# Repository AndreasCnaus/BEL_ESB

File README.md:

# Hardware Setup
- RF Breakout Board (see also Hardware Section)
- Bosch BME280 Sensor
- RF-Antenna

# Verification with nRF-Connect

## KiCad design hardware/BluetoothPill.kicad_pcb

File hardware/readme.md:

# RF Breakout Board

USB Powered STM32WB55 based breakout board for wireless applications within 2.4GHz ISM-Band (e.g BLE). 

# Characteristics
Input Voltage-Range: &nbsp; 3.4V - 5.5V <br>
Output Voltage: &nbsp; 3.3V <br>
Crystals: &nbsp; HSE: 32MHz, LSE: 32.768kHz <br> 
MCU: &nbsp; STM32WB55CEU6 <br>
SMPS-Support: &nbsp;  for low power mode <br>
BOOT0/User-Button: &nbsp; boots from USB when pushed during power up <br>
LED's:  &nbsp; Power-Led (orange), User-Led (blue) <br>
Serial Wire Debug with Tag-Connec <br>

## Connectivity
USB-FS with 12Mb/s <br>
I2C1: &nbsp; (SDA, SCL) <br>
UART1: &nbsp; (Tx, Rx) <br>
SPI1: &nbsp; (NSS, SCK, MISO, MOSI) <br>
RF: &nbsp; 2.4GHz ISM-Band, BLE 5.4, IEEE 802.15.4 (Zigbee 3.0, Thread 1.3) <br>

# Links
This board was designed according to the following tutorial with a few changes: &nbsp; https://youtu.be/nkHFoxe0mrU?si=10UZT0h6SDpFT777 <br>
STM32WB55-Datasheet: &nbsp; https://www.st.com/resource/en/datasheet/stm32wb55cc.pdf <br>

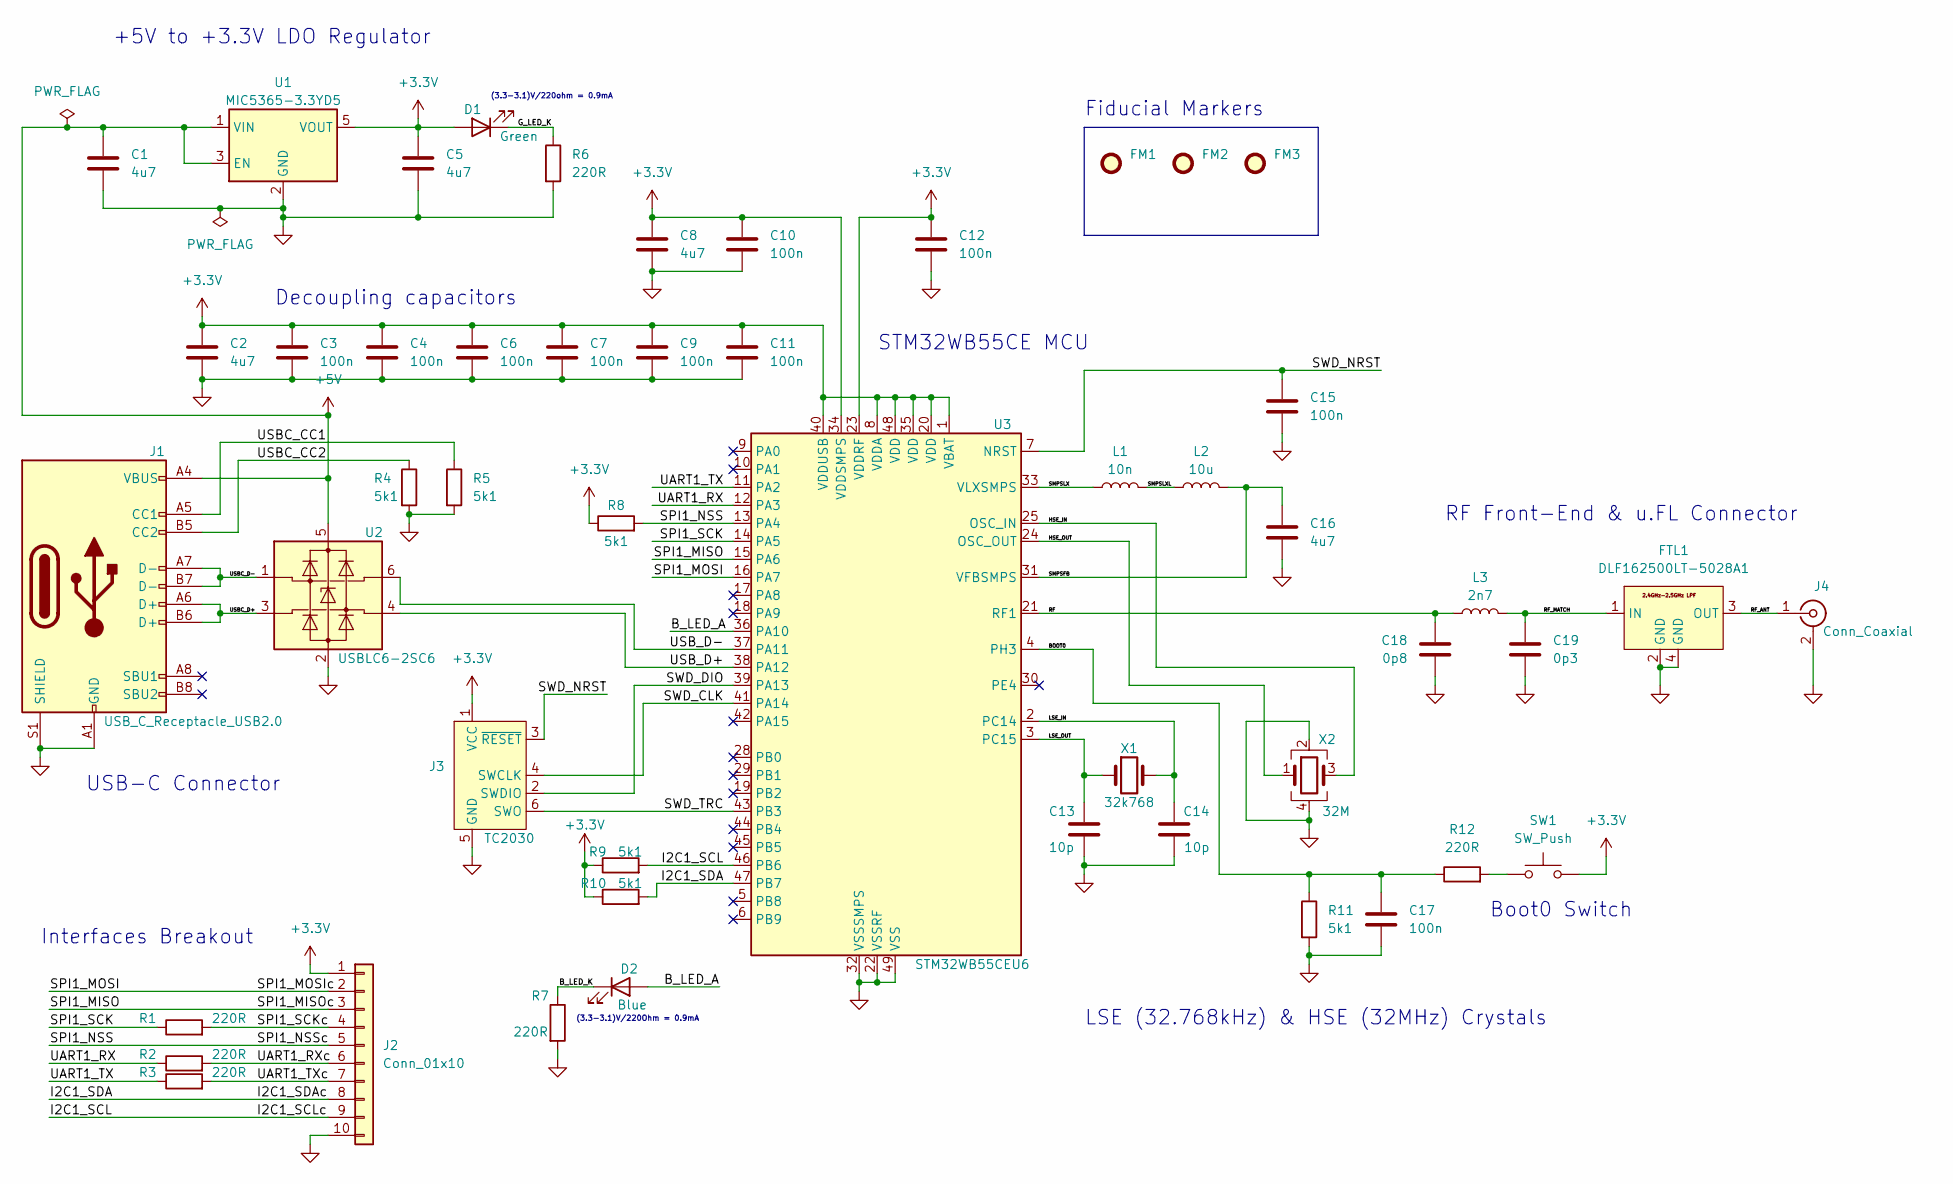
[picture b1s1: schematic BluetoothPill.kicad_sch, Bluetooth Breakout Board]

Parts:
C1, C2, C5, C8, C16: 4u7; C_0603_1608Metric; Manufacturer Part Numb KGM15CR51E475KT
C3, C4, C6, C7, C9, C10, C11, C12, C15, C17: 100n; C_0402_1005Metric; Manufacturer Part Numb 885012205086
C13, C14: 10p; C_0402_1005Metric; Manufacturer Part Numb C0402C100K8HACAUTO
C18: 0p8; C_0402_1005Metric; Manufacturer Part Numb GRM1555C1HR80BA01D
C19: 0p3; C_0402_1005Metric; Manufacturer Part Numb GRM1555C1HR30WA01D
D1: Green; LED_0402_1005Metric; Manufacturer Part Numb LTST-C281KGKT
D2: Blue; LED_0402_1005Metric; Manufacturer Part Numb VLMB1500-GS08
FM1, FM2, FM3: Fiducial; Fiducial_1mm_Mask2mm
FTL1: DLF162500LT-5028A1; Manufacturer Part Numb DLF162500LT-5028A1
J1: USB_C_Receptacle_USB2.0; USB_C_Receptacle_GCT_USB4105-xx-A_16P_TopMnt_Horizontal; Manufacturer Part Numb USB4105-GF-A
J2: Conn_01x10; PinHeader_1x10_P2.54mm_Vertical
J3: TC2030; Tag-Connect_TC2030-IDC-FP_2x03_P1.27mm_Vertical
J4: Conn_Coaxial; U.FL_Hirose_U.FL-R-SMT-1_Vertical; Manufacturer Part Numb U.FL-R-SMT(01)
L1: 10n; L_0402_1005Metric; Manufacturer Part Numb LQG15WZ10NJ02D
L2: 10u; L_0805_2012Metric; Manufacturer Part Numb LQM21FN100M70L
L3: 2n7; L_0402_1005Metric; Manufacturer Part Numb LQG15HS2N7S02D
R1, R2, R3, R6, R7, R12: 220R; R_0402_1005Metric; Manufacturer Part Numb AF0402JR-07220RL
R4, R5, R8, R9, R10, R11: 5k1; R_0402_1005Metric; Manufacturer Part Numb ERJ-2RKF5101X
SW1: SW_Push; SW_SPST_CK_RS282G05A3; Manufacturer Part Numb RS282G05A3SMRT
U1: MIC5365-3.3YD5; SOT-23-5; Manufacturer Part Numb MIC5365-3.3YD5-TR
U2: USBLC6-2SC6; SOT-23-6; Manufacturer Part Numb USBLC6-2SC6
U3: STM32WB55CEU6; QFN-48-1EP_7x7mm_P0.5mm_EP5.6x5.6mm; Manufacturer Part Numb STM32WB55CEU6
X1: 32k768; Crystal_SMD_2012-2Pin_2.0x1.2mm; Manufacturer Part Numb NX2012SA-32.768K-STD-MUB-1
X2: 32M; Crystal_SMD_2016-4Pin_2.0x1.6mm; Manufacturer Part Numb NX2016SA-32M-EXS00A-CS06465

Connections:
+3.3V: C2.1, C3.1, C4.1, C5.1, C6.1, C7.1, C8.1, C9.1, C10.1, C11.1, C12.1, D1.2 (A), J2.1, J3.1 (VCC), R8.1, R9.1, R10.1, SW1.2, U1.5 (VOUT), U3.1 (VBAT), U3.8 (VDDA), U3.20 (VDD), U3.23 (VDDRF), U3.34 (VDDSMPS), U3.35 (VDD), U3.40 (VDDUSB), U3.48 (VDD)
+5V: C1.1, J1.A4 (VBUS), J1.A9 (VBUS), J1.B4 (VBUS), J1.B9 (VBUS), U1.1 (VIN), U1.3 (EN), U2.5 (VBUS)
/BOOT0: C17.1, R11.1, R12.1, U3.4 (PH3)
/B_LED_A: D2.2 (A), U3.36 (PA10)
/B_LED_K: D2.1 (K), R7.1
/G_LED_K: D1.1 (K), R6.1
/HSE_IN: U3.25 (OSC_IN), X2.3
/HSE_OUT: U3.24 (OSC_OUT), X2.1
/I2C1_SCL: J2.9, R9.2, U3.46 (PB6)
/I2C1_SDA: J2.8, R10.2, U3.47 (PB7)
/LSE_IN: C14.1, U3.2 (PC14), X1.2
/LSE_OUT: C13.1, U3.3 (PC15), X1.1
/RF: C18.1, L3.1, U3.21 (RF1)
/RF_ANT: FTL1.3 (OUT), J4.1 (In)
/RF_MATCH: C19.1, FTL1.1 (IN), L3.2
/SMPSFB: C16.1, L2.2, U3.31 (VFBSMPS)
/SMPSLX: L1.1, U3.33 (VLXSMPS)
/SMPSLXL: L1.2, L2.1
/SPI1_MISO: J2.3, U3.15 (PA6)
/SPI1_MOSI: J2.2, U3.16 (PA7)
/SPI1_NSS: J2.5, R8.2, U3.13 (PA4)
/SPI1_SCK: R1.1, U3.14 (PA5)
/SPI1_SCKc: J2.4, R1.2
/SWD_CLK: J3.4 (SWCLK), U3.41 (PA14)
/SWD_DIO: J3.2 (SWDIO), U3.39 (PA13)
/SWD_NRST: C15.1, J3.3 (~RESET), U3.7 (NRST)
/SWD_TRC: J3.6 (SWO), U3.43 (PB3)
/UART1_RX: R2.1, U3.12 (PA3)
/UART1_RXc: J2.6, R2.2
/UART1_TX: R3.1, U3.11 (PA2)
/UART1_TXc: J2.7, R3.2
/USBC_CC1: J1.A5 (CC1), R5.1
/USBC_CC2: J1.B5 (CC2), R4.1
/USBC_D+: J1.A6 (D+), J1.B6 (D+), U2.3 (I/O1)
/USBC_D-: J1.A7 (D-), J1.B7 (D-), U2.1 (I/O1)
/USB_D+: U2.4 (I/O2), U3.38 (PA12)
/USB_D-: U2.6 (I/O2), U3.37 (PA11)
GND: C1.2, C2.2, C3.2, C4.2, C5.2, C6.2, C7.2, C8.2, C9.2, C10.2, C11.2, C12.2, C13.2, C14.2, C15.2, C16.2, C17.2, C18.2, C19.2, FTL1.2 (GND), FTL1.4 (GND), J1.A1 (GND), J1.A12 (GND), J1.B1 (GND), J1.B12 (GND), J1.S1 (SHIELD), J2.10, J3.5 (GND), J4.2 (Ext), R4.2, R5.2, R6.2, R7.2, R11.2, U1.2 (GND), U2.2 (GND), U3.22 (VSSRF), U3.32 (VSSSMPS), U3.49 (VSS), X2.2, X2.4
unnamed: R12.2, SW1.1

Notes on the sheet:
Fiducial Markers
USB-C Connector
RF Front-End & u.FL Connector
+5V to +3.3V LDO Regulator
(3.3-3.1)V/220Ohm = 0.9mA
LSE (32.768kHz) & HSE (32MHz) Crystals
Interfaces Breakout
Decoupling capacitors
Boot0 Switch
(3.3-3.1)V/220ohm = 0.9mA
STM32WB55CE MCU

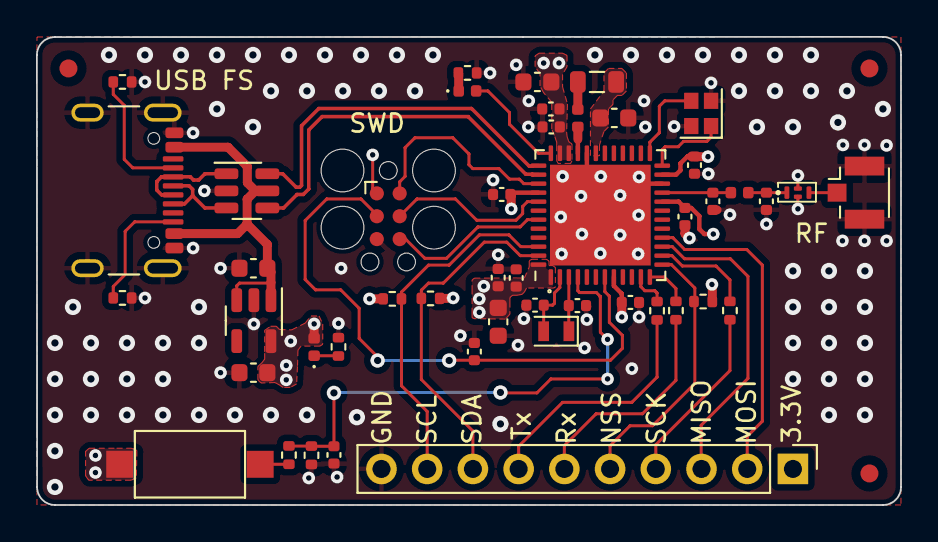
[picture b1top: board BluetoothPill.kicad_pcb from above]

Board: 4 copper layers, 48.0 x 26.0 mm, 50 parts (0 on the bottom side), 39 nets.

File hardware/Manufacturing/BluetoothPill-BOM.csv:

Designator,Quantity,Value,Footprint,Description,Manufacturer,Manufacturer Part Number,Distributor Link
"C1, C2, C5, C8, C16",5,4u7,Capacitor_SMD:C_0603_1608Metric,Unpolarized capacitor,KYOCERA AVX,KGM15CR51E475KT,https://www.mouser.de/ProductDetail/KYOCERA-AVX/KGM15CR51E47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
"C3, C4, C6, C7, C9, C10, C11, C12, C15, C17",10,100n,Capacitor_SMD:C_0402_1005Metric,Unpolarized capacitor,Wurth Elektronik,885012205086,https://www.mouser.de/ProductDetail/Wurth-Elektronik/8850122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
"C13, C14",2,10p,Capacitor_SMD:C_0402_1005Metric,Unpolarized capacitor,KEMET,C0402C100K8HACAUTO,https://www.mouser.de/ProductDetail/KEMET/C0402C100K8HACAUTO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
C18,1,0p8,Capacitor_SMD:C_0402_1005Metric,Unpolarized capacitor,Murata Electronics,GRM1555C1HR80BA01D,https://www.mouser.de/ProductDetail/Murata-Electronics/GRM15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
C19,1,0p3,Capacitor_SMD:C_0402_1005Metric,Unpolarized capacitor,Murata Electronics,GRM1555C1HR30WA01D,https://www.mouser.de/ProductDetail/Murata-Electronics/GRM15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
D1,1,Green,LED_SMD:LED_0402_1005Metric,Light emitting diode,Lite-On,LTST-C281KGKT,https://www.mouser.de/ProductDetail/Lite-On/LTST-C281KGKT?qs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
D2,1,Blue,LED_SMD:LED_0402_1005Metric,Light emitting diode,Vishay Semiconductors,VLMB1500-GS08,https://www.mouser.de/ProductDetail/Vishay-Semiconductors/VL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
FTL1,1,DLF162500LT-5028A1,custom:DLF162500LT-5028A1,RF-Lowpass filter,TDK,DLF162500LT-5028A1,https://www.mouser.de/ProductDetail/TDK/DLF162500LT-5028A1?q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
J1,1,USB_C_Receptacle_USB2.0,Connector_USB:USB_C_Receptacle_GCT_USB4105-xx-A_16P_TopMnt_Horizontal,USB 2.0-only Type-C Receptacle connector,GCT,USB4105-GF-A,https://www.mouser.de/ProductDetail/GCT/USB4105-GF-A?qs=KUoI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
J4,1,Conn_Coaxial,Connector_Coaxial:U.FL_Hirose_U.FL-R-SMT-1_Vertical,"coaxial connector (BNC, SMA, SMB, SMC, Cinch/RCA, LEMO, ...)",Hirose Connector,U.FL-R-SMT(01),https://www.mouser.de/ProductDetail/Hirose-Connector/U.FL-R-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
L1,1,10n,Inductor_SMD:L_0402_1005Metric,Inductor,Murata Electronics,LQG15WZ10NJ02D,https://www.mouser.de/ProductDetail/Murata-Electronics/LQG15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
L2,1,10u,Inductor_SMD:L_0805_2012Metric,Inductor,Murata Electronics,LQM21FN100M70L,https://www.mouser.de/ProductDetail/Murata-Electronics/LQM21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
L3,1,2n7,Inductor_SMD:L_0402_1005Metric,Inductor,Murata Electronics,LQG15HS2N7S02D,https://www.mouser.de/ProductDetail/Murata-Electronics/LQG15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
"R1, R2, R3, R6, R7, R12",6,220R,Resistor_SMD:R_0402_1005Metric,Resistor,YAGEO,AF0402JR-07220RL,https://www.mouser.de/ProductDetail/YAGEO/AF0402JR-07220RL?q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
"R4, R5, R8, R9, R10, R11",6,5k1,Resistor_SMD:R_0402_1005Metric,Resistor,Panasonic,ERJ-2RKF5101X,https://www.mouser.de/ProductDetail/Panasonic/ERJ-2RKF5101X?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
SW1,1,SW_Push,Button_Switch_SMD:SW_SPST_CK_RS282G05A3,"Push button switch, generic, two pins",C&K,RS282G05A3SMRT,https://www.mouser.de/ProductDetail/CK/RS282G05A3SMRT?qs=Guf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
U1,1,MIC5365-3.3YD5,Package_TO_SOT_SMD:SOT-23-5,"150mA Low-dropout Voltage Regulator, Vout 3.3V, Vin up to 5.5V, SOT-23-5",Microchip Technology,MIC5365-3.3YD5-TR,https://www.mouser.de/ProductDetail/Microchip-Technology/MIC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
U2,1,USBLC6-2SC6,Package_TO_SOT_SMD:SOT-23-6,"Very low capacitance ESD protection diode, 2 data-line, SOT-23-6",STMicroelectronics,USBLC6-2SC6,https://www.mouser.de/ProductDetail/STMicroelectronics/USBLC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
U3,1,STM32WB55CEU6,Package_DFN_QFN:QFN-48-1EP_7x7mm_P0.5mm_EP5.6x5.6mm,"STMicroelectronics Arm Cortex-M4 MCU, 512KB flash, 256KB RAM, 64 MHz, 1.71-3.6V, 30 GPIO, UFQFPN48",STMicroelectronics,STM32WB55CEU6,https://www.mouser.de/ProductDetail/STMicroelectronics/STM32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
X1,1,32k768,Crystal:Crystal_SMD_2012-2Pin_2.0x1.2mm,Two pin crystal,NDK,NX2012SA-32.768K-STD-MUB-1,https://www.mouser.de/ProductDetail/NDK/NX2012SA-32.768K-STD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
X2,1,32M,Crystal:Crystal_SMD_2016-4Pin_2.0x1.6mm,"Four pin crystal, GND on pins 2 and 4",NDK,NX2016SA-32M-EXS00A-CS06465,https://www.mouser.de/ProductDetail/NDK/NX2016SA-32M-EXS00A-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

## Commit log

2024-11-08 hardware section added
2024-11-08 Update Hardware readme.md
    KiCAD 7.0 Board view added
2024-11-08 software section added
2024-11-08 Update software readme.md
    Hardware pinout configuration view added
2024-11-08 Project description added
2024-11-08 Update Project README.md
    Pictures of the board prototype and the nRF verification app added to the project description
2024-11-08 Improvements in timer_flag and pressure convert..
    preventing of potential race conditions by using timer-flag and improvement of
    pressure convertation for nRF-App
2024-11-08 Update main.c : handling of irq
    Disabling of irq could be critical because of BLE stack which relies on interrupts. Since race conditions are not really important in this case, this will be left out for now
